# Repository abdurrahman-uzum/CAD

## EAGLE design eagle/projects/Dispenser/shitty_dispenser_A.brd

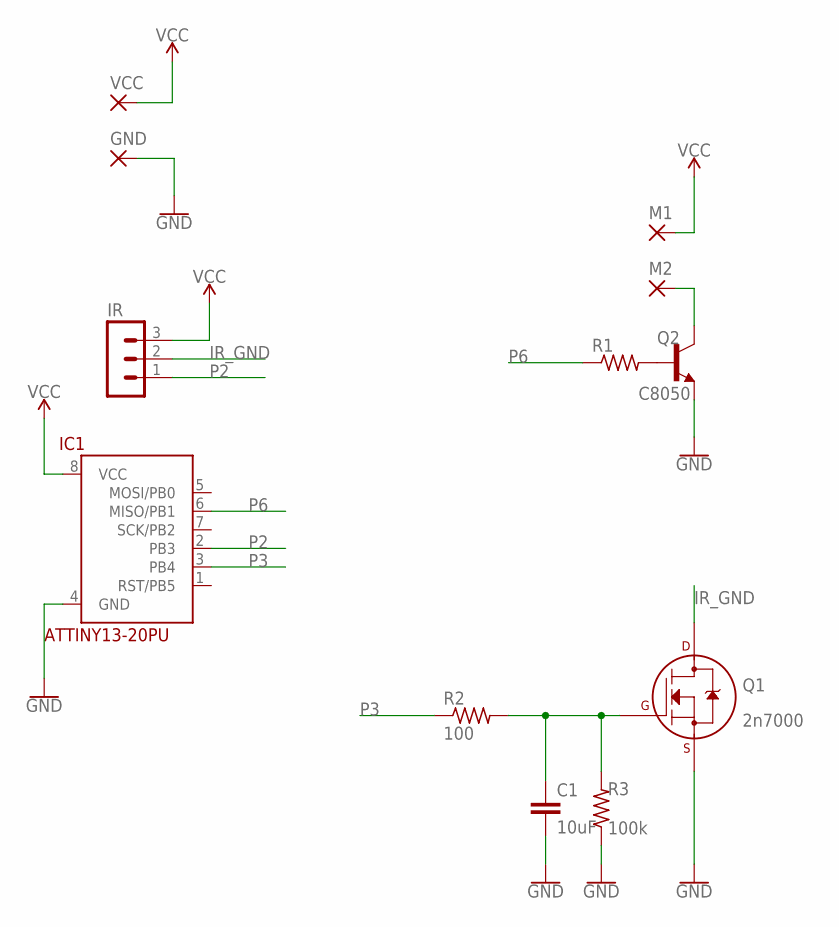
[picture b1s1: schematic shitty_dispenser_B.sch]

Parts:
C1: 10uF; C025-025X050
GND: 2,54/1,0
IC1: ATTINY13-20PU; DIL08
IR: MA03-1
M1, M2: 2,54/1,0
Q1: 2n7000; TO92-
Q2: C8050; TO92-EBC
R1: R-US_0204/7; 0204/7
R2: 100; 0204/7
R3: 100k; 0204/7
VCC: 2,54/1,0

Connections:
GND: C1.2, GND.1, IC1.4 (GND), Q1.3 (S), Q2.E, R3.1
IR_GND: IR.2, Q1.1 (D)
unnamed: C1.1, Q1.2 (G), R2.2, R3.2
unnamed: Q2.B, R1.2
unnamed: M2.1, Q2.C
P2: IC1.2 (PB3), IR.1
P3: IC1.3 (PB4), R2.1
P6: IC1.6 (MISO/PB1), R1.1
VCC: IC1.8 (VCC), IR.3, M1.1, VCC.1

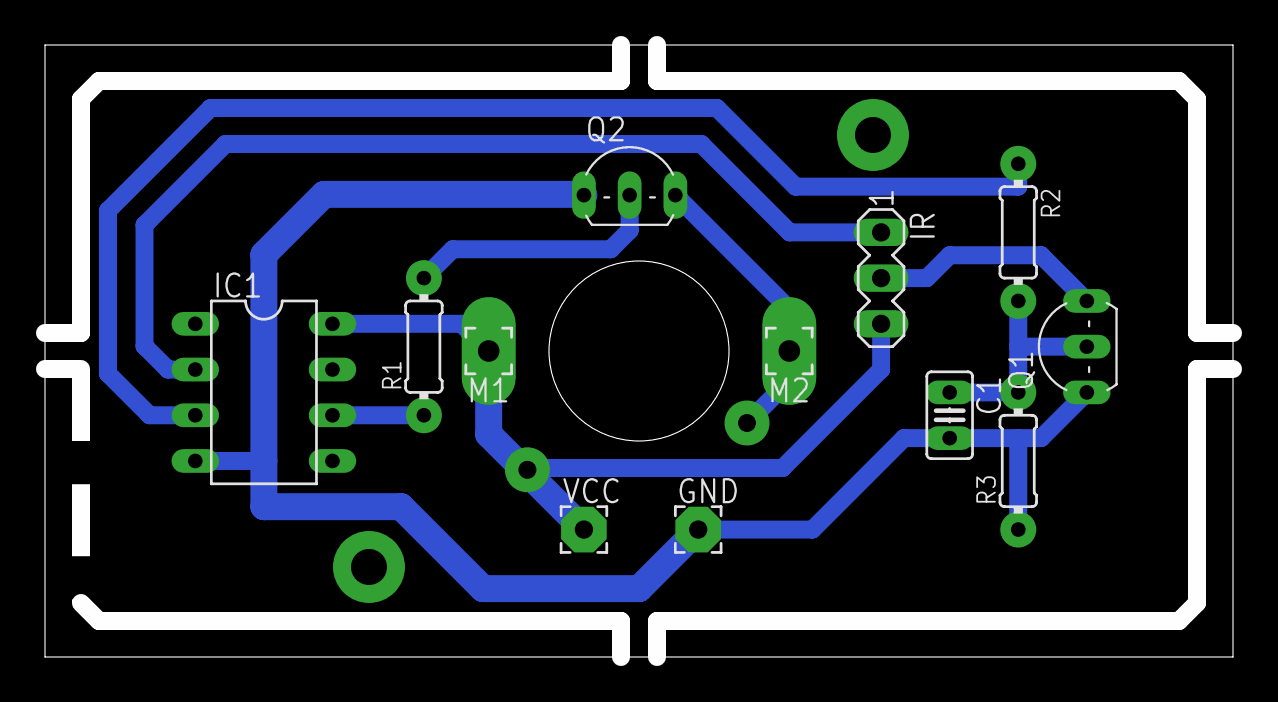
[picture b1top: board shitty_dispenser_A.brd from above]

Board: 2 copper layers, 66.0 x 34.0 mm, 12 parts (0 on the bottom side), 9 nets.

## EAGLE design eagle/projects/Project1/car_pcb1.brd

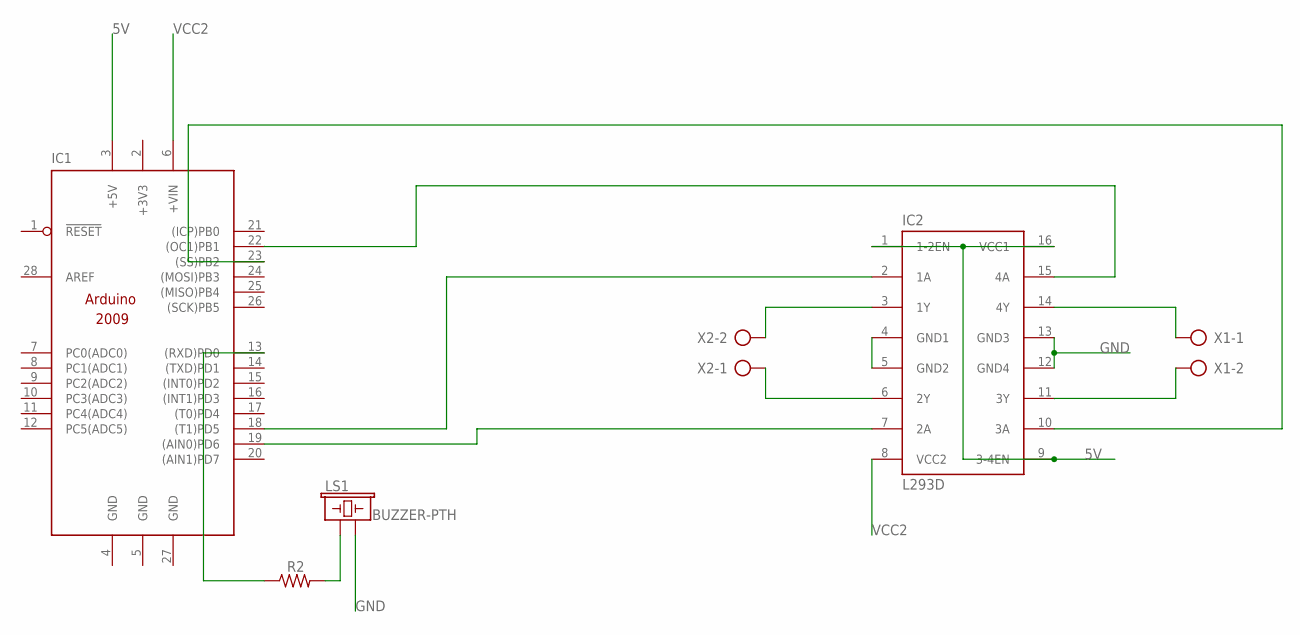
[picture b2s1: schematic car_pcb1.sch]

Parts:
IC1: ARDUINO2009_PIN_10; ARDUINO2009
IC2: L293D; DIL16
LS1: BUZZER-PTH; BUZZER-12MM
R2: R-US_0204/7; 0204/7
X1, X2: AK500/2

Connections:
5V: IC1.3 (+5V), IC2.1 (1-2EN), IC2.9 (3-4EN), IC2.16 (VCC1)
+3V3: IC1.2 (+3V3)
GND: IC1.4 (GND), IC1.5 (GND), IC1.27 (GND), IC2.12 (GND4), IC2.13 (GND3), LS1.- (2)
unnamed: IC1.18 ((T1)PD5), IC2.2 (1A)
unnamed: IC1.19 ((AIN0)PD6), IC2.7 (2A)
unnamed: IC2.3 (1Y), X2.2
unnamed: IC2.6 (2Y), X2.1
unnamed: IC2.14 (4Y), X1.1
unnamed: IC2.11 (3Y), X1.2
unnamed: IC2.4 (GND1), IC2.5 (GND2)
unnamed: IC1.22 ((OC1)PB1), IC2.15 (4A)
unnamed: IC1.23 ((SS)PB2), IC2.10 (3A)
unnamed: LS1.+ (1), R2.2
unnamed: IC1.13 ((RXD)PD0), R2.1
VCC2: IC1.6 (+VIN), IC2.8 (VCC2)

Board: 2 copper layers, 6 parts (0 on the bottom side), 14 nets, no tracks yet.

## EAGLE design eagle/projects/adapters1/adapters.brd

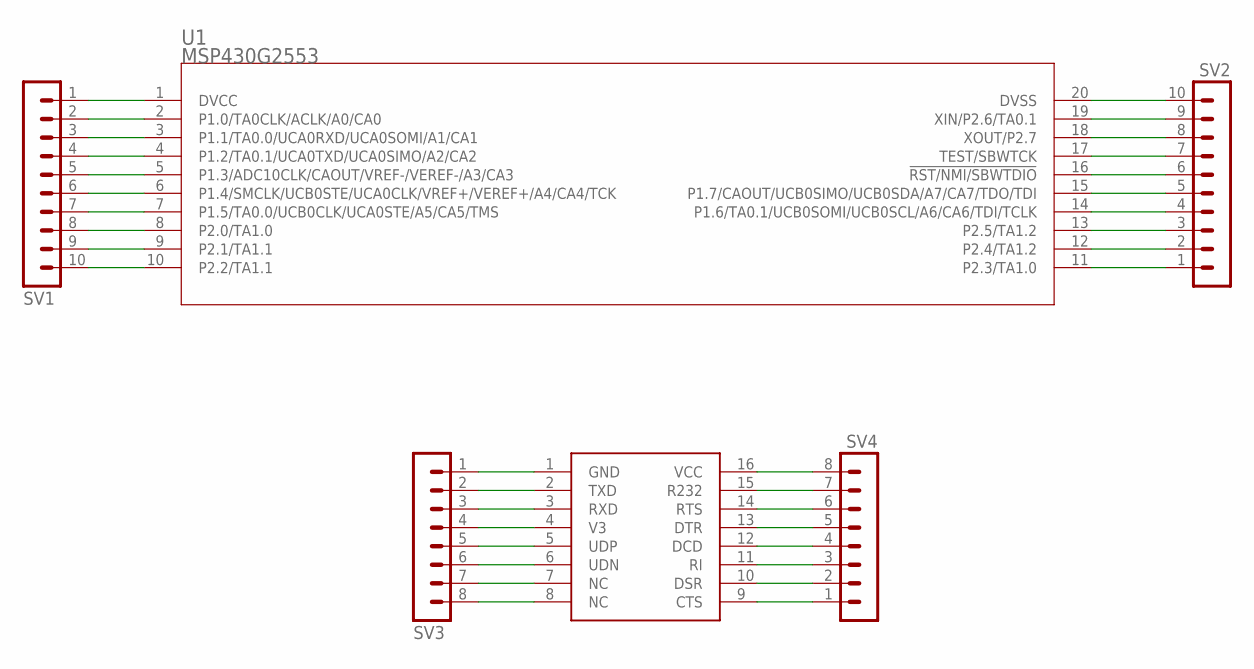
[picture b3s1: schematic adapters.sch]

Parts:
SV1, SV2: MA10-1
SV3, SV4: MA08-1
U1: MSP430G2553; PW20-M
U$1: CH340; SOP16

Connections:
unnamed: SV1.1, U1.1 (DVCC)
unnamed: SV1.2, U1.2 (P1.0/TA0CLK/ACLK/A0/CA0)
unnamed: SV1.3, U1.3 (P1.1/TA0.0/UCA0RXD/UCA0SOMI/A1/CA1)
unnamed: SV1.4, U1.4 (P1.2/TA0.1/UCA0TXD/UCA0SIMO/A2/CA2)
unnamed: SV1.5, U1.5 (P1.3/ADC10CLK/CAOUT/VREF-/VEREF-/A3/CA3)
unnamed: SV1.6, U1.6 (P1.4/SMCLK/UCB0STE/UCA0CLK/VREF+/VEREF+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)
unnamed: SV1.7, U1.7 (P1.5/TA0.0/UCB0CLK/UCA0STE/A5/CA5/TMS)
unnamed: SV1.8, U1.8 (P2.0/TA1.0)
unnamed: SV1.9, U1.9 (P2.1/TA1.1)
unnamed: SV1.10, U1.10 (P2.2/TA1.1)
unnamed: SV2.1, U1.11 (P2.3/TA1.0)
unnamed: SV2.2, U1.12 (P2.4/TA1.2)
unnamed: SV2.3, U1.13 (P2.5/TA1.2)
unnamed: SV2.4, U1.14 (P1.6/TA0.1/UCB0SOMI/UCB0SCL/A6/CA6/TDI/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)
unnamed: SV2.5, U1.15 (P1.7/CAOUT/UCB0SIMO/UCB0SDA/A7/CA7/TDO/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)
unnamed: SV2.6, U1.16 (!RST/NMI/SBWTDIO)
unnamed: SV2.7, U1.17 (TEST/SBWTCK)
unnamed: SV2.8, U1.18 (XOUT/P2.7)
unnamed: SV2.9, U1.19 (XIN/P2.6/TA0.1)
unnamed: SV2.10, U1.20 (DVSS)
unnamed: SV3.1, U$1.1 (GND)
unnamed: SV3.2, U$1.2 (TXD)
unnamed: SV3.3, U$1.3 (RXD)
unnamed: SV3.4, U$1.4 (V3)
unnamed: SV3.5, U$1.5 (UDP)
unnamed: SV3.6, U$1.6 (UDN)
unnamed: SV3.7, U$1.7 (NC)
unnamed: SV3.8, U$1.8 (NC)
unnamed: SV4.1, U$1.9 (CTS)
unnamed: SV4.2, U$1.10 (DSR)
unnamed: SV4.3, U$1.11 (RI)
unnamed: SV4.4, U$1.12 (DCD)
unnamed: SV4.5, U$1.13 (DTR)
unnamed: SV4.6, U$1.14 (RTS)
unnamed: SV4.7, U$1.15 (R232)
unnamed: SV4.8, U$1.16 (VCC)

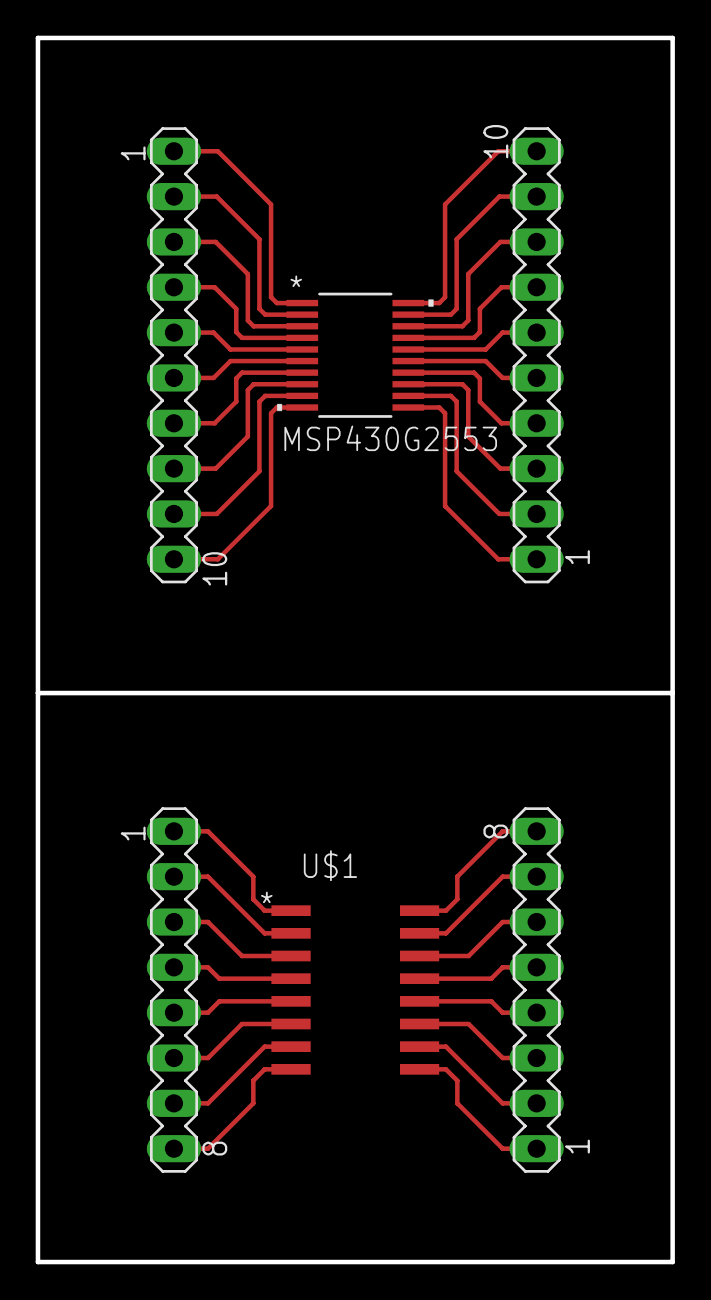
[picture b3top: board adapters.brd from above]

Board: 2 copper layers, 35.6 x 68.6 mm, 6 parts (0 on the bottom side), 36 nets.

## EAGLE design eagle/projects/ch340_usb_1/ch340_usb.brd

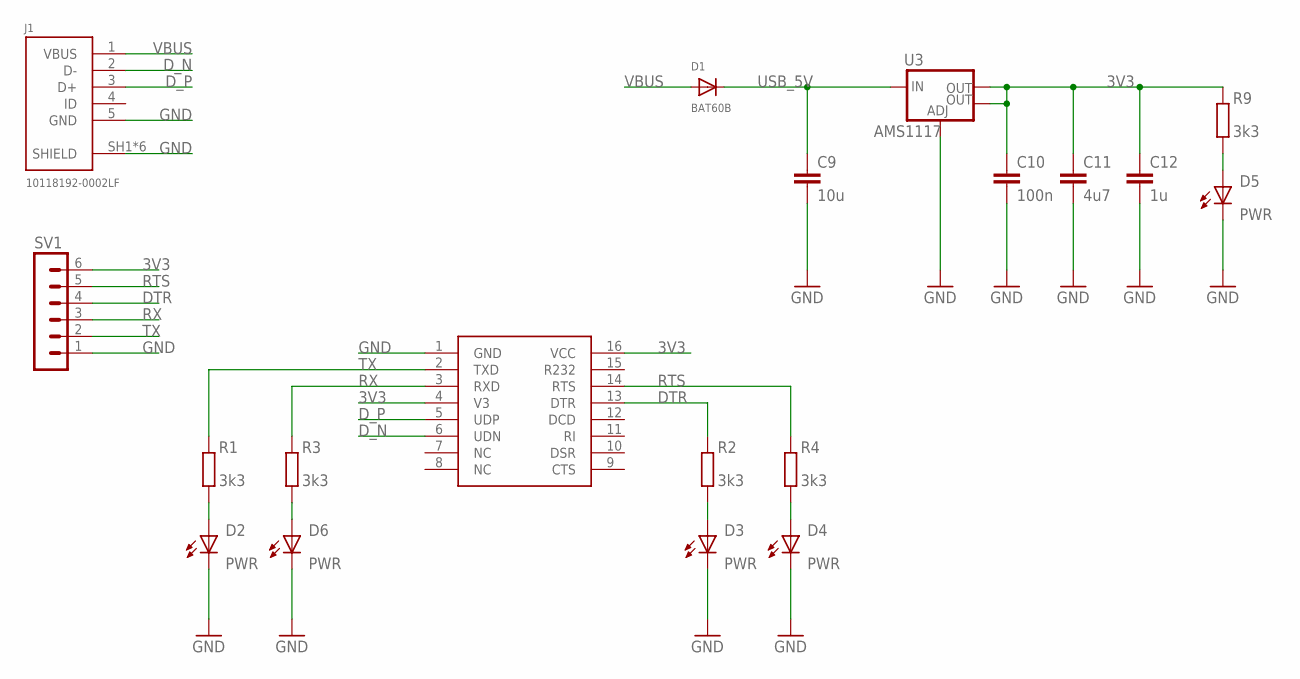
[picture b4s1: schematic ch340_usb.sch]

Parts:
C9: 10u; C0603
C10: 100n; C0603
C11: 4u7; C0603
C12: 1u; C0603
D1: BAT60B; SOD-323F
D2, D3, D4, D5, D6: PWR; CHIPLED_0805
J1: 10118192-0002LF
R1, R2, R3, R4, R9: 3k3; R0603
SV1: MA06-1
U3: AMS1117; SOT223
U$1: CH340; SOP16

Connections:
3V3: C10.1, C11.1, C12.1, R9.2, SV1.6, U3.2 (OUT), U3.4 (OUT), U$1.4 (V3), U$1.16 (VCC)
DTR: R2.2, SV1.4, U$1.13 (DTR)
D_N: J1.2 (D-), U$1.6 (UDN)
D_P: J1.3 (D+), U$1.5 (UDP)
GND: C9.2, C10.2, C11.2, C12.2, D2.C, D3.C, D4.C, D5.C, D6.C, J1.5 (GND), J1.SH1 (SHIELD), J1.SH2 (SHIELD), J1.SH3 (SHIELD), J1.SH4 (SHIELD), J1.SH5 (SHIELD), J1.SH6 (SHIELD), SV1.1, U3.1 (ADJ), U$1.1 (GND)
unnamed: D2.A, R1.1
unnamed: D6.A, R3.1
unnamed: D3.A, R2.1
unnamed: D4.A, R4.1
unnamed: D5.A, R9.1
RTS: R4.2, SV1.5, U$1.14 (RTS)
RX: R3.2, SV1.3, U$1.3 (RXD)
TX: R1.2, SV1.2, U$1.2 (TXD)
USB_5V: C9.1, D1.C, U3.3 (IN)
VBUS: D1.A, J1.1 (VBUS)

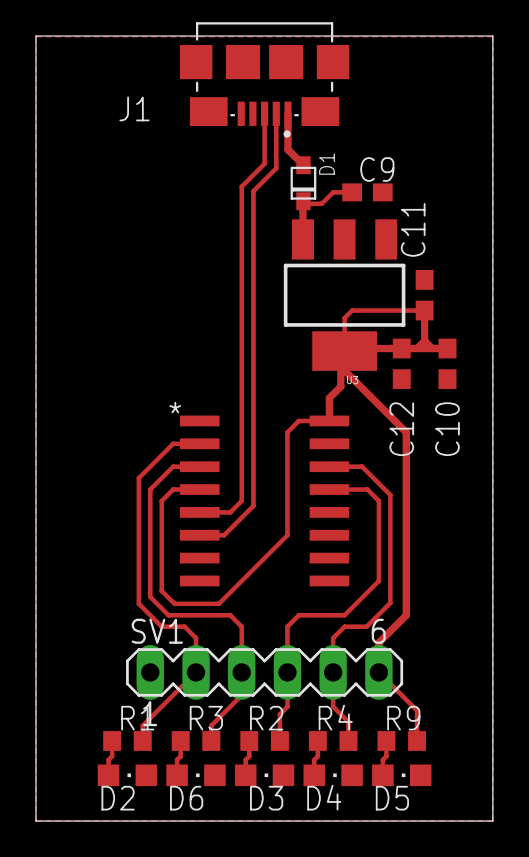
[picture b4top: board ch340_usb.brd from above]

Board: 2 copper layers, 25.4 x 43.6 mm, 19 parts (0 on the bottom side), 15 nets.

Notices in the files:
parts and their libraries:
SparkFun-PowerSymbols: Licensing: Creative Commons ShareAlike 4.0 International - https://creativecommons.org/licenses/by-sa/4.0
COPYRIGHT: Copyright (C) 2023 Ultra Librarian. All rights reserved.
